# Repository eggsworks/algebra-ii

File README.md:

## Algebra II

A keyboard designed to be broken

### What?

This keyboard can be many things:

- A 3x7 ortho with a 4u "numrow"
- A 3x5, 3x6, or 3x7 split with 2, 3, or 4 thumb keys
- A 3x5, 3x6, or 3x7 macropad

### Why?

Why not?

### What happened to Algebra I?

No further questions, thank you

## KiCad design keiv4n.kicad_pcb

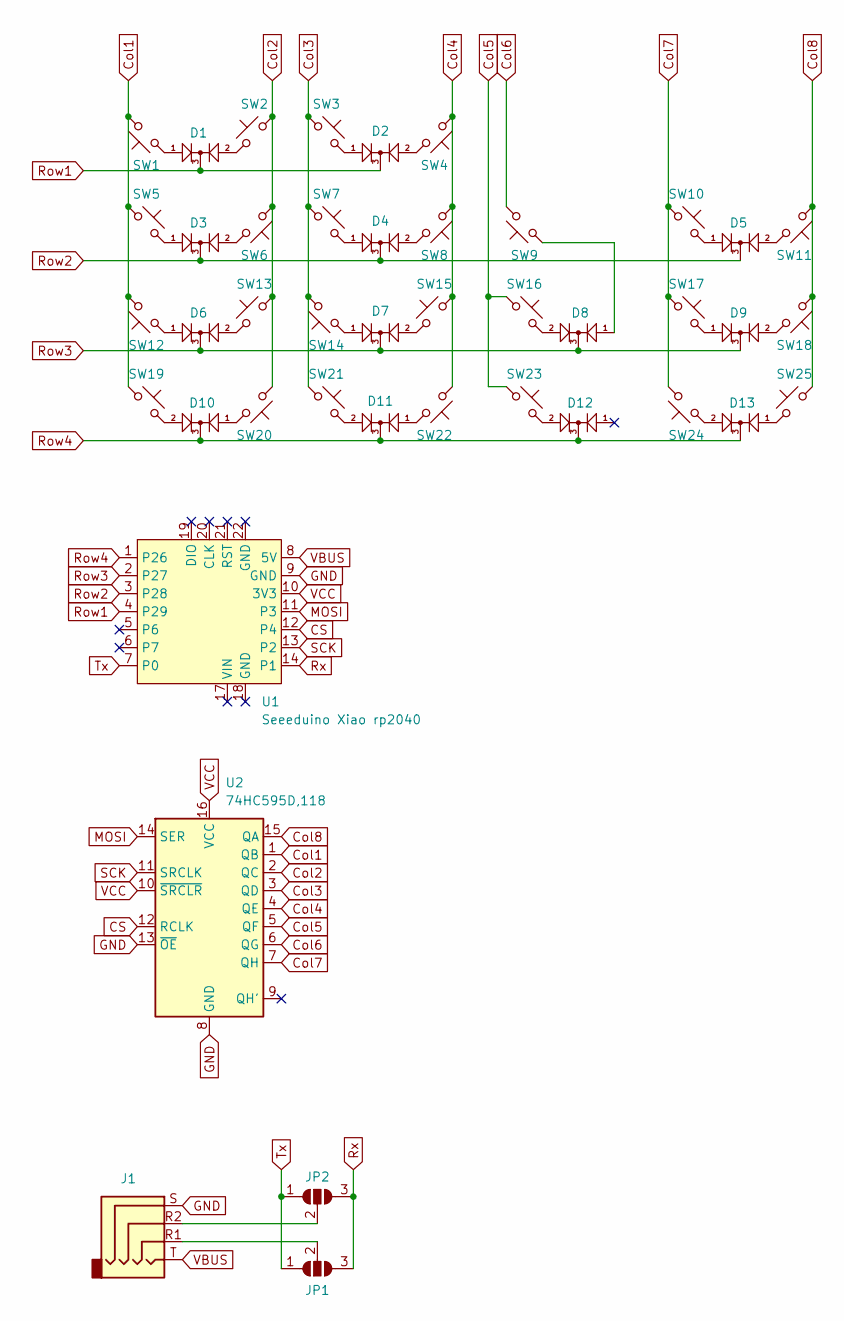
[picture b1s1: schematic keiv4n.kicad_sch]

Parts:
D1, D2, D3, D4, D5, D6, D7, D8, D9, D10, D11, D12, D13: BAV70_Small; SOT-23
J1: AudioJack4; CON_MJ-4PP-9_Reversible
JP1, JP2: SolderJumper_3_Open; SolderJumper-3_P1.3mm_Open_RoundedPad1.0x1.5mm
SW1, SW2, SW3, SW4, SW5, SW6, SW7, SW8, SW9, SW10, SW11, SW12, SW13, SW14, SW15, SW16, SW17, SW18, SW19, SW20, SW21, SW22, SW23, SW24, SW25: SW_Push_45deg; SW_MX_Reversible_1u
U1: Seeeduino Xiao rp2040; Xiao_rp2040_AH_Pogo
U2: 74HC595D,118; SOIC-16_3.9x9.9mm_P1.27mm

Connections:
CS: U1.12 (P4), U2.12 (RCLK)
Col1: SW1.2, SW5.1, SW12.2, SW19.1, U2.1 (QB)
Col2: SW2.1, SW6.2, SW13.1, SW20.2, U2.2 (QC)
Col3: SW3.1, SW7.1, SW14.2, SW21.1, U2.3 (QD)
Col4: SW4.2, SW8.2, SW15.1, SW22.2, U2.4 (QE)
Col5: SW16.1, SW23.1, U2.5 (QF)
Col6: SW9.2, U2.6 (QG)
Col7: SW10.1, SW17.1, SW24.2, U2.7 (QH)
Col8: SW11.2, SW18.2, SW25.1, U2.15 (QA)
GND: J1.S, U1.9 (GND), U2.8 (GND), U2.13 (~OE)
MOSI: U1.11 (P3), U2.14 (SER)
unnamed: D1.1 (A1), SW1.1
unnamed: D1.2 (A2), SW2.2
unnamed: D2.1 (A1), SW3.2
unnamed: D2.2 (A2), SW4.1
unnamed: D3.1 (A1), SW5.2
unnamed: D3.2 (A2), SW6.1
unnamed: D4.1 (A1), SW7.2
unnamed: D4.2 (A2), SW8.1
unnamed: D5.1 (A1), SW10.2
unnamed: D5.2 (A2), SW11.1
unnamed: D6.1 (A1), SW12.1
unnamed: D6.2 (A2), SW13.2
unnamed: D7.1 (A1), SW14.1
unnamed: D7.2 (A2), SW15.2
unnamed: D8.1 (A1), SW9.1
unnamed: D8.2 (A2), SW16.2
unnamed: D9.1 (A1), SW17.2
unnamed: D9.2 (A2), SW18.1
unnamed: D10.1 (A1), SW20.1
unnamed: D10.2 (A2), SW19.2
unnamed: D11.1 (A1), SW22.1
unnamed: D11.2 (A2), SW21.2
unnamed: D12.2 (A2), SW23.2
unnamed: D13.1 (A1), SW25.2
unnamed: D13.2 (A2), SW24.1
unnamed: J1.R1, JP1.2 (C)
unnamed: J1.R2, JP2.2 (C)
Row1: D1.3 (K), D2.3 (K), U1.4 (P29)
Row2: D3.3 (K), D4.3 (K), D5.3 (K), U1.3 (P28)
Row3: D6.3 (K), D7.3 (K), D8.3 (K), D9.3 (K), U1.2 (P27)
Row4: D10.3 (K), D11.3 (K), D12.3 (K), D13.3 (K), U1.1 (P26)
Rx: JP1.3 (B), JP2.3 (B), U1.14 (P1)
SCK: U1.13 (P2), U2.11 (SRCLK)
Tx: JP1.1 (A), JP2.1 (A), U1.7 (P0)
VBUS: J1.T, U1.8 (5V)
VCC: U1.10 (3V3), U2.10 (~SRCLR), U2.16 (VCC)

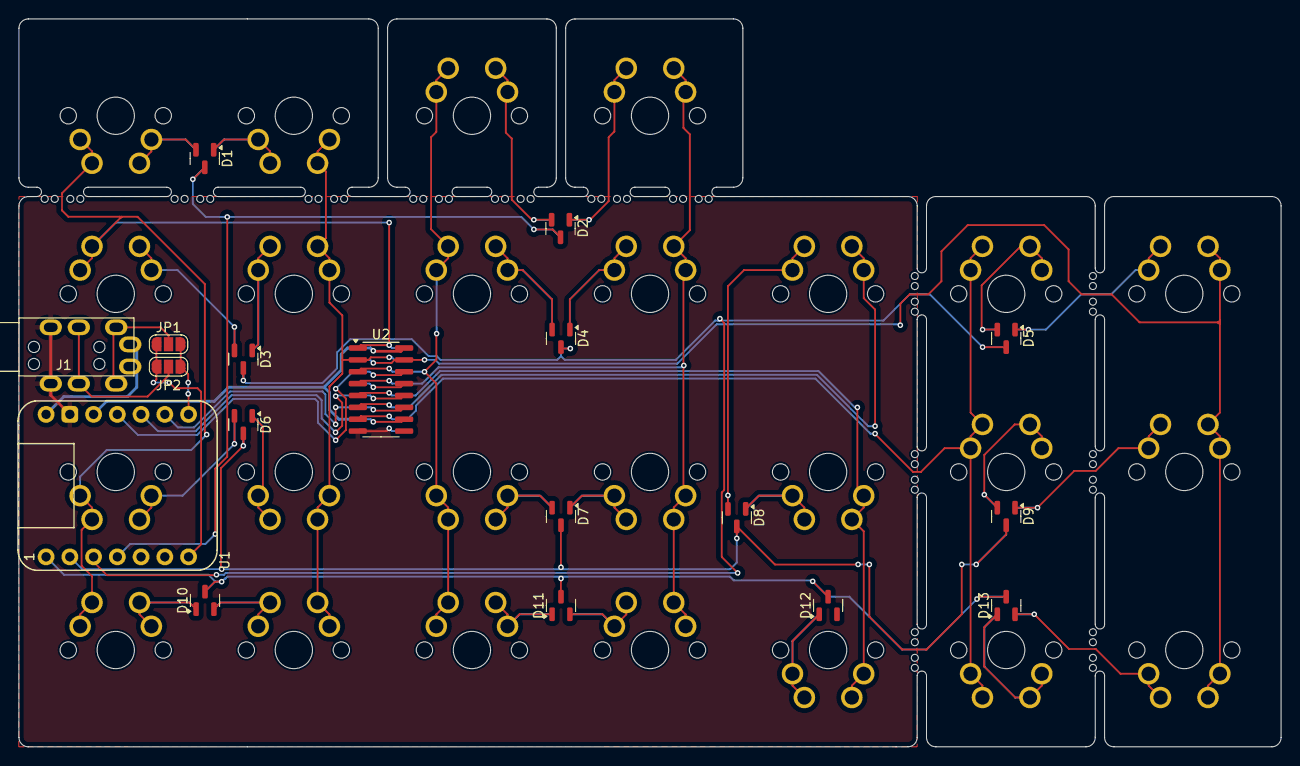
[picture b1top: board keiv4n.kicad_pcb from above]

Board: 2 copper layers, 135.0 x 77.9 mm, 43 parts (0 on the bottom side), 47 nets.

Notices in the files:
keiv4n.kicad_pcb:
© 2024
